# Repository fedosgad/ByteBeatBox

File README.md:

# ByteBeatBox
Pocket bytebeat device

This repo (will) contain(s) PCB files (KiCad) and (maybe) alternative firmware.

See also [main firmware repo](https://github.com/Bredian/PROJECT_BYTEBEAT/tree/master)

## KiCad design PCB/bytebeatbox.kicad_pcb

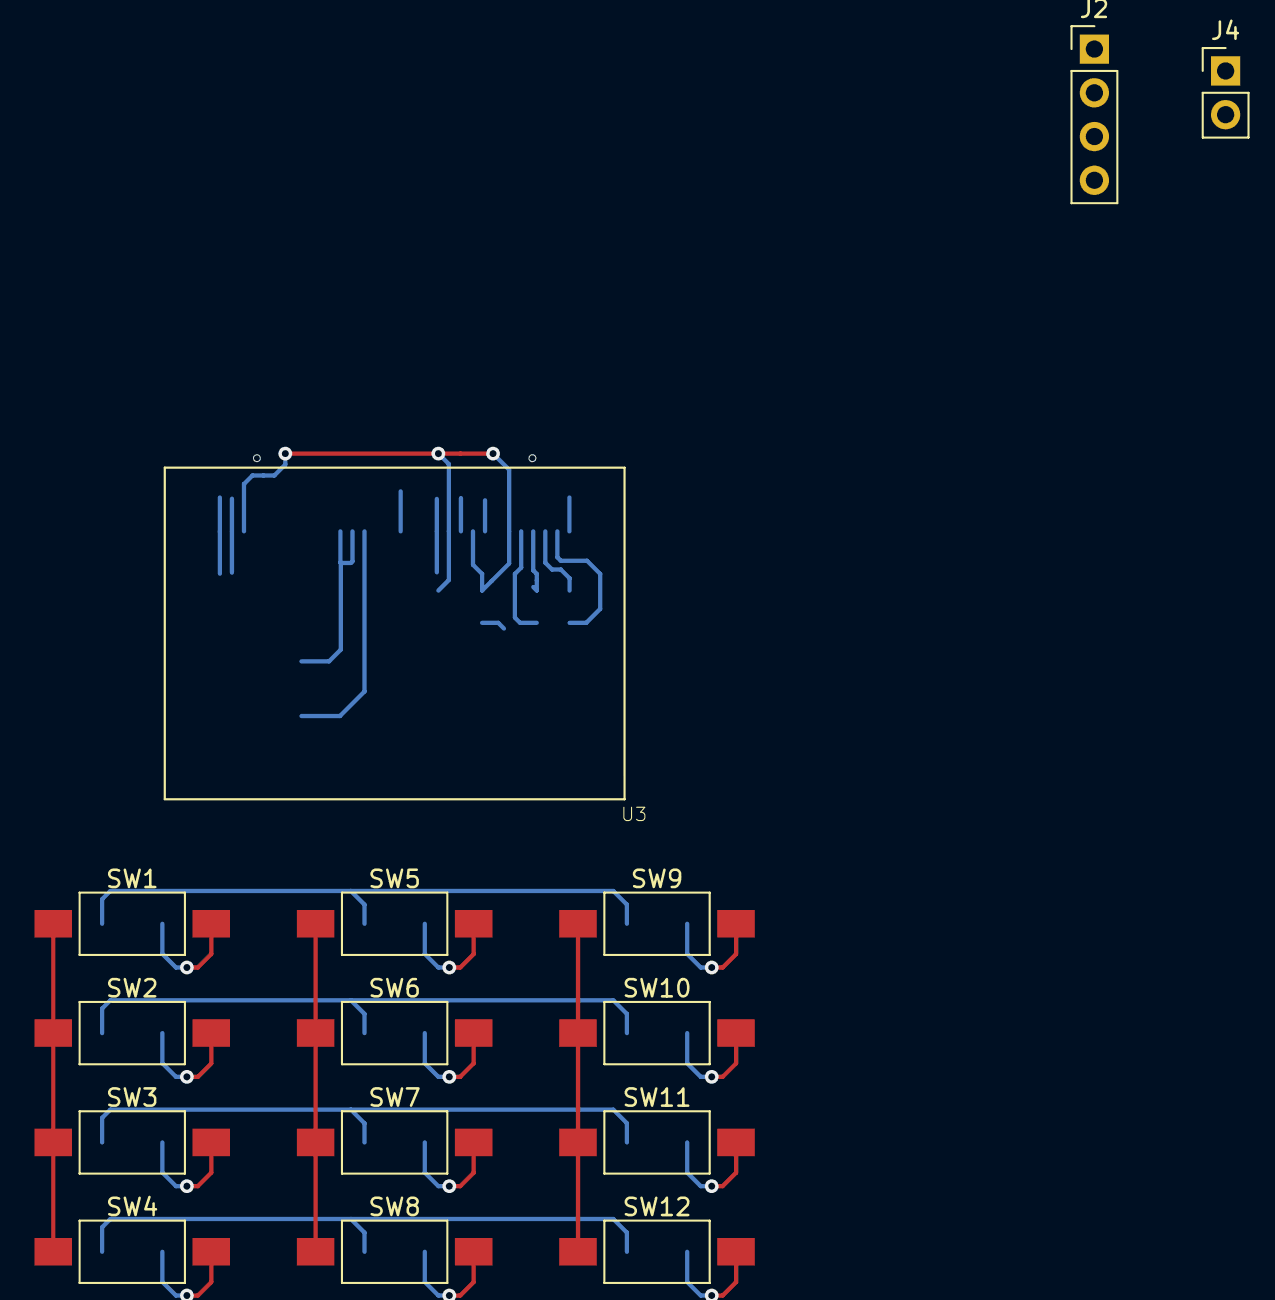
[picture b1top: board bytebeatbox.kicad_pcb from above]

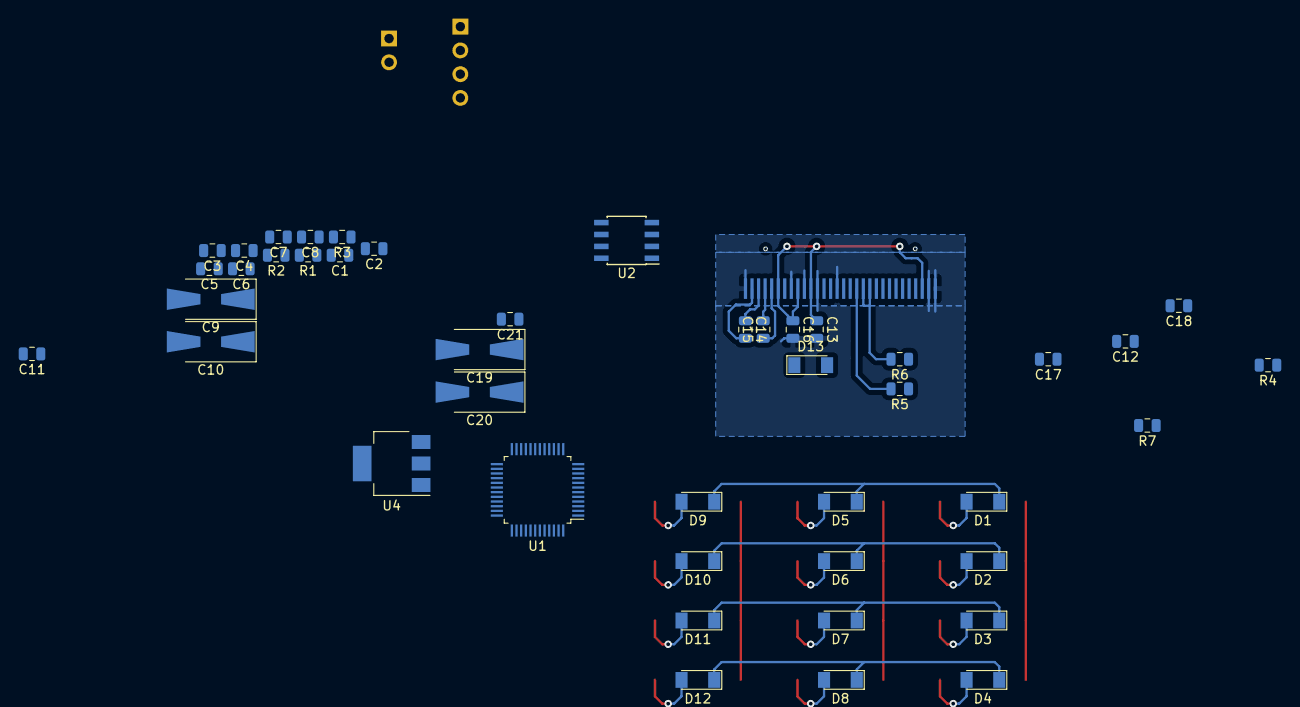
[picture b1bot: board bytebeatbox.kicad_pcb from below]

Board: 2 copper layers, 59 parts (44 on the bottom side), 38 nets.

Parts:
C1, C2, C3, C4, C5, C6, C7, C8, C11: 100n; C_0805_2012Metric
C9, C10, C19, C20: 10u; D_SMA-SMB_Universal_Handsoldering
C12, C18: 10u; C_0805_2012Metric
C13, C14, C15, C16: 1u; C_0805_2012Metric
C17: 2.2u/16V; C_0805_2012Metric
C21: 4.7u; C_0805_2012Metric
D1, D2, D3, D4, D5, D6, D7, D8, D9, D10, D11, D12, D13: D; D_MiniMELF
J2: SWD; PinHeader_1x04_P2.54mm_Vertical
J4: Power; PinHeader_1x02_P2.54mm_Vertical
R1: dnp; R_0805_2012Metric
R2, R3, R5, R6, R7: 10k; R_0805_2012Metric
R4: 390k; R_0805_2012Metric
SW1, SW2, SW3, SW4, SW5, SW6, SW7, SW8, SW9, SW10, SW11, SW12: SW_Push_45deg; SW_SPST_FSMSM
U1: STM32F100C8Tx; LQFP-48_7x7mm_P0.5mm
U2: LM358; SOIC-8_3.9x4.9mm_P1.27mm
U3: DISP_OLED_UG-2864HSWEG01; UG-2864HSWEG01_0.96IN_WRAPAROUND
U4: AZ1117-3.3; SOT-223-3_TabPin2

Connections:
+3V3: C1.1, C3.1, C4.2, C5.1, C6.1, C7.1, C8.1, C9.1, C10.1, C12.2, C13.1, C16.1, C20.1, C21.1, D13.1, J2.1, R1.1, R3.1, R5.1, R6.1, R7.1, U1.1, U1.9, U1.24, U1.36, U1.48, U3.6, U3.9, U3.11, U3.28, U4.2
+5V: C11.1, C19.1, J4.1, U2.8, U4.3
/AUDIO_OUT: U1.14, U2.3, U2.5
/C0: SW1.1, SW2.1, SW3.1, SW4.1, U1.16
/C1: SW5.1, SW6.1, SW7.1, SW8.1, U1.17
/C2: SW9.1, SW10.1, SW11.1, SW12.1, U1.29
/I2C_SCK: R5.2, U1.42, U3.18
/R0: D1.1, D5.1, D9.1, U1.30
/R1: D2.1, D6.1, D10.1, U1.31
/R2: D3.1, D7.1, D11.1, U1.32
/R3: D4.1, D8.1, D12.1, U1.33
/SDA: R6.2, U1.43, U3.19, U3.20
/SWCLK: J2.3, U1.37
/SWDIO: J2.2, U1.34
GND: C1.2, C2.2, C3.2, C4.1, C5.2, C6.2, C7.2, C8.2, C9.2, C10.2, C11.2, C12.1, C13.2, C16.2, C17.1, C18.2, C19.2, C20.2, C21.2, J2.4, J4.2, R2.2, R4.1, U1.8, U1.23, U1.35, U1.47, U2.4, U3.1, U3.8, U3.10, U3.12, U3.15, U3.29, U3.30, U4.1
unnamed: C2.1, R3.2, U1.7
unnamed: C14.1, U3.3
unnamed: C14.2, U3.2
unnamed: C15.1, U3.5
unnamed: C15.2, U3.4
unnamed: C17.2, U3.27
unnamed: C18.1, D13.2, R7.2, U3.14
unnamed: D1.2, SW1.2
unnamed: D2.2, SW2.2
unnamed: D3.2, SW3.2
unnamed: D4.2, SW4.2
unnamed: D5.2, SW5.2
unnamed: D6.2, SW6.2
unnamed: D7.2, SW7.2
unnamed: D8.2, SW8.2
unnamed: D9.2, SW9.2
unnamed: D10.2, SW10.2
unnamed: D11.2, SW11.2
unnamed: D12.2, SW12.2
unnamed: U2.6, U2.7
unnamed: U2.1, U2.2
unnamed: R1.2, R2.1, U1.44
unnamed: R4.2, U3.26

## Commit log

2018-09-26 Added KiCad files and edited README
